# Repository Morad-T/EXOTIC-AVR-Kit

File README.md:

# AVR Kit

AVR Dev. Kit based on the ATmega32A

## Features

- Only 2 Layer PCB
- Can accomodate ZIF or normal 40-Pin sockets
- Over Current Protection
- CH340C USB to UART Interface
- Power Rail Selector
- Direct 10-Pin ISP Interface

## Yet To Be Done

- ICSP Header
- EMC Simulations

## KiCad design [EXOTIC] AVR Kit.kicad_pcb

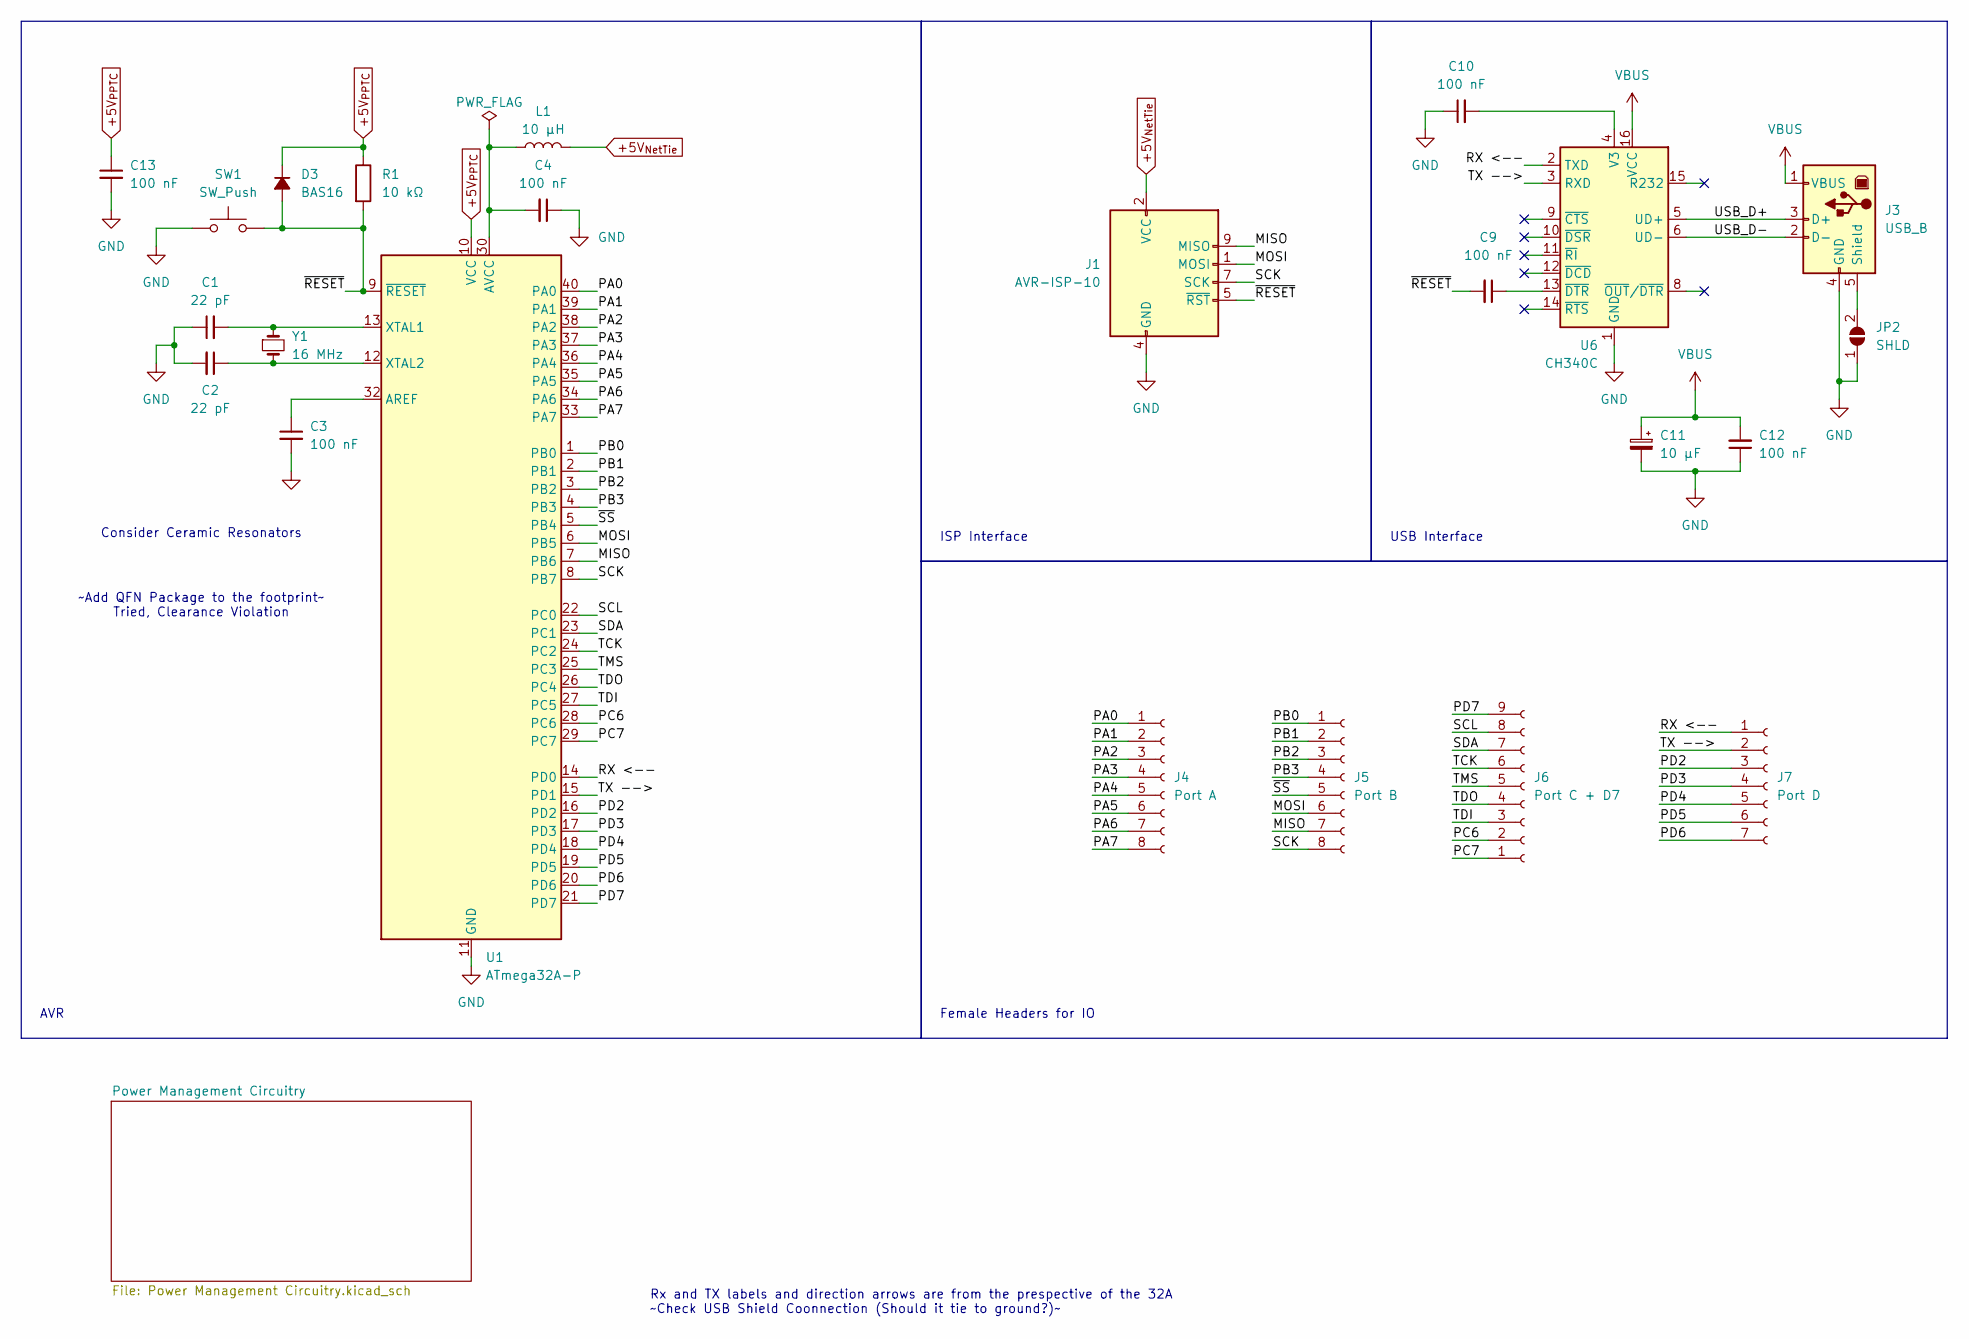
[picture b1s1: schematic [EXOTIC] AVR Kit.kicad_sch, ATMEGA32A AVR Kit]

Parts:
C1, C2: 22 pF; C_1206_3216Metric_Pad1.33x1.80mm_HandSolder
C3, C4, C9, C10, C12, C13: 100 nF; C_1206_3216Metric_Pad1.33x1.80mm_HandSolder
C11: 10 µF; C_1206_3216Metric_Pad1.33x1.80mm_HandSolder
D3: BAS16; SOT-23_Handsoldering
J1: AVR-ISP-10; IDC-Header_2x05_P2.54mm_Vertical
J3: USB_B; USB_B_Connector_Horizontal
J4: Port A; PinSocket_1x08_P2.54mm_Vertical
J5: Port B; PinSocket_1x08_P2.54mm_Vertical
J6: Port C + D7; PinSocket_1x09_P2.54mm_Vertical
J7: Port D; PinSocket_1x07_P2.54mm_Vertical
JP2: SHLD; SolderJumper-2_P1.3mm_Open_RoundedPad1.0x1.5mm
L1: 10 µH; L_1206_3216Metric_Pad1.22x1.90mm_HandSolder
R1: 10 kΩ; R_1206_3216Metric_Pad1.30x1.75mm_HandSolder
SW1: SW_Push; SW_PUSH_6mm_H4.3mm
U1: ATmega32A-P; ZIF_Socket_40_Circular_Pads
U6: CH340C; SOIC-16_3.9x9.9mm_P1.27mm
Y1: 16 MHz; Crystal_HC49-4H_Vertical_Centered

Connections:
+5V_{NetTie}: J1.2 (VCC), L1.1; also elsewhere on the board
+5V_{PPTC}: C13.1, D3.1 (K), R1.1, U1.10 (VCC); also elsewhere on the board
/MISO: J1.9 (MISO), J5.7, U1.7 (PB6)
/MOSI: J1.1 (MOSI), J5.6, U1.6 (PB5)
/PA0: J4.1, U1.40 (PA0)
/PA1: J4.2, U1.39 (PA1)
/PA2: J4.3, U1.38 (PA2)
/PA3: J4.4, U1.37 (PA3)
/PA4: J4.5, U1.36 (PA4)
/PA5: J4.6, U1.35 (PA5)
/PA6: J4.7, U1.34 (PA6)
/PA7: J4.8, U1.33 (PA7)
/PB0: J5.1, U1.1 (PB0)
/PB1: J5.2, U1.2 (PB1)
/PB2: J5.3, U1.3 (PB2)
/PB3: J5.4, U1.4 (PB3)
/PC6: J6.2, U1.28 (PC6)
/PC7: J6.1, U1.29 (PC7)
/PD2: J7.3, U1.16 (PD2)
/PD3: J7.4, U1.17 (PD3)
/PD4: J7.5, U1.18 (PD4)
/PD5: J7.6, U1.19 (PD5)
/PD6: J7.7, U1.20 (PD6)
/PD7: J6.9, U1.21 (PD7)
/RX <--: J7.1, U1.14 (PD0), U6.2 (TXD)
/SCK: J1.7 (SCK), J5.8, U1.8 (PB7)
/SCL: J6.8, U1.22 (PC0)
/SDA: J6.7, U1.23 (PC1)
/TCK: J6.6, U1.24 (PC2)
/TDI: J6.3, U1.27 (PC5)
/TDO: J6.4, U1.26 (PC4)
/TMS: J6.5, U1.25 (PC3)
/TX -->: J7.2, U1.15 (PD1), U6.3 (RXD)
/USB_D+: J3.3 (D+), U6.5 (UD+)
/USB_D-: J3.2 (D-), U6.6 (UD-)
/~RESET: C9.2, D3.2 (A), J1.5 (~RST), R1.2, SW1.1, U1.9 (~RESET)
/~SS: J5.5, U1.5 (PB4)
GND: C1.1, C2.2, C3.2, C4.1, C10.1, C11.2, C12.1, C13.2, J1.4 (GND), J1.6 (GND), J1.8 (GND), J1.10 (GND), J3.4 (GND), JP2.1 (A), SW1.2, U1.11 (GND), U1.31 (GND), U6.1 (GND); also elsewhere on the board
unnamed: J3.5 (Shield), JP2.2 (B)
unnamed: C3.1, U1.32 (AREF)
unnamed: C4.2, L1.2, U1.30 (AVCC)
unnamed: C1.2, U1.13 (XTAL1), Y1.1
unnamed: C2.1, U1.12 (XTAL2), Y1.2
unnamed: C10.2, U6.4 (V3)
unnamed: C9.1, U6.13 (~DTR)
VBUS: C11.1, C12.2, J3.1 (VBUS), U6.16 (VCC); also elsewhere on the board

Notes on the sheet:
Female Headers for IO
AVR
~Add QFN Package to the footprint~ Tried, Clearance Violation
ISP Interface
Consider Ceramic Resonators
Rx and TX labels and direction arrows are from the prespective of the 32A ~Check USB Shield Coonnection (Should it tie to ground?)~
USB Interface

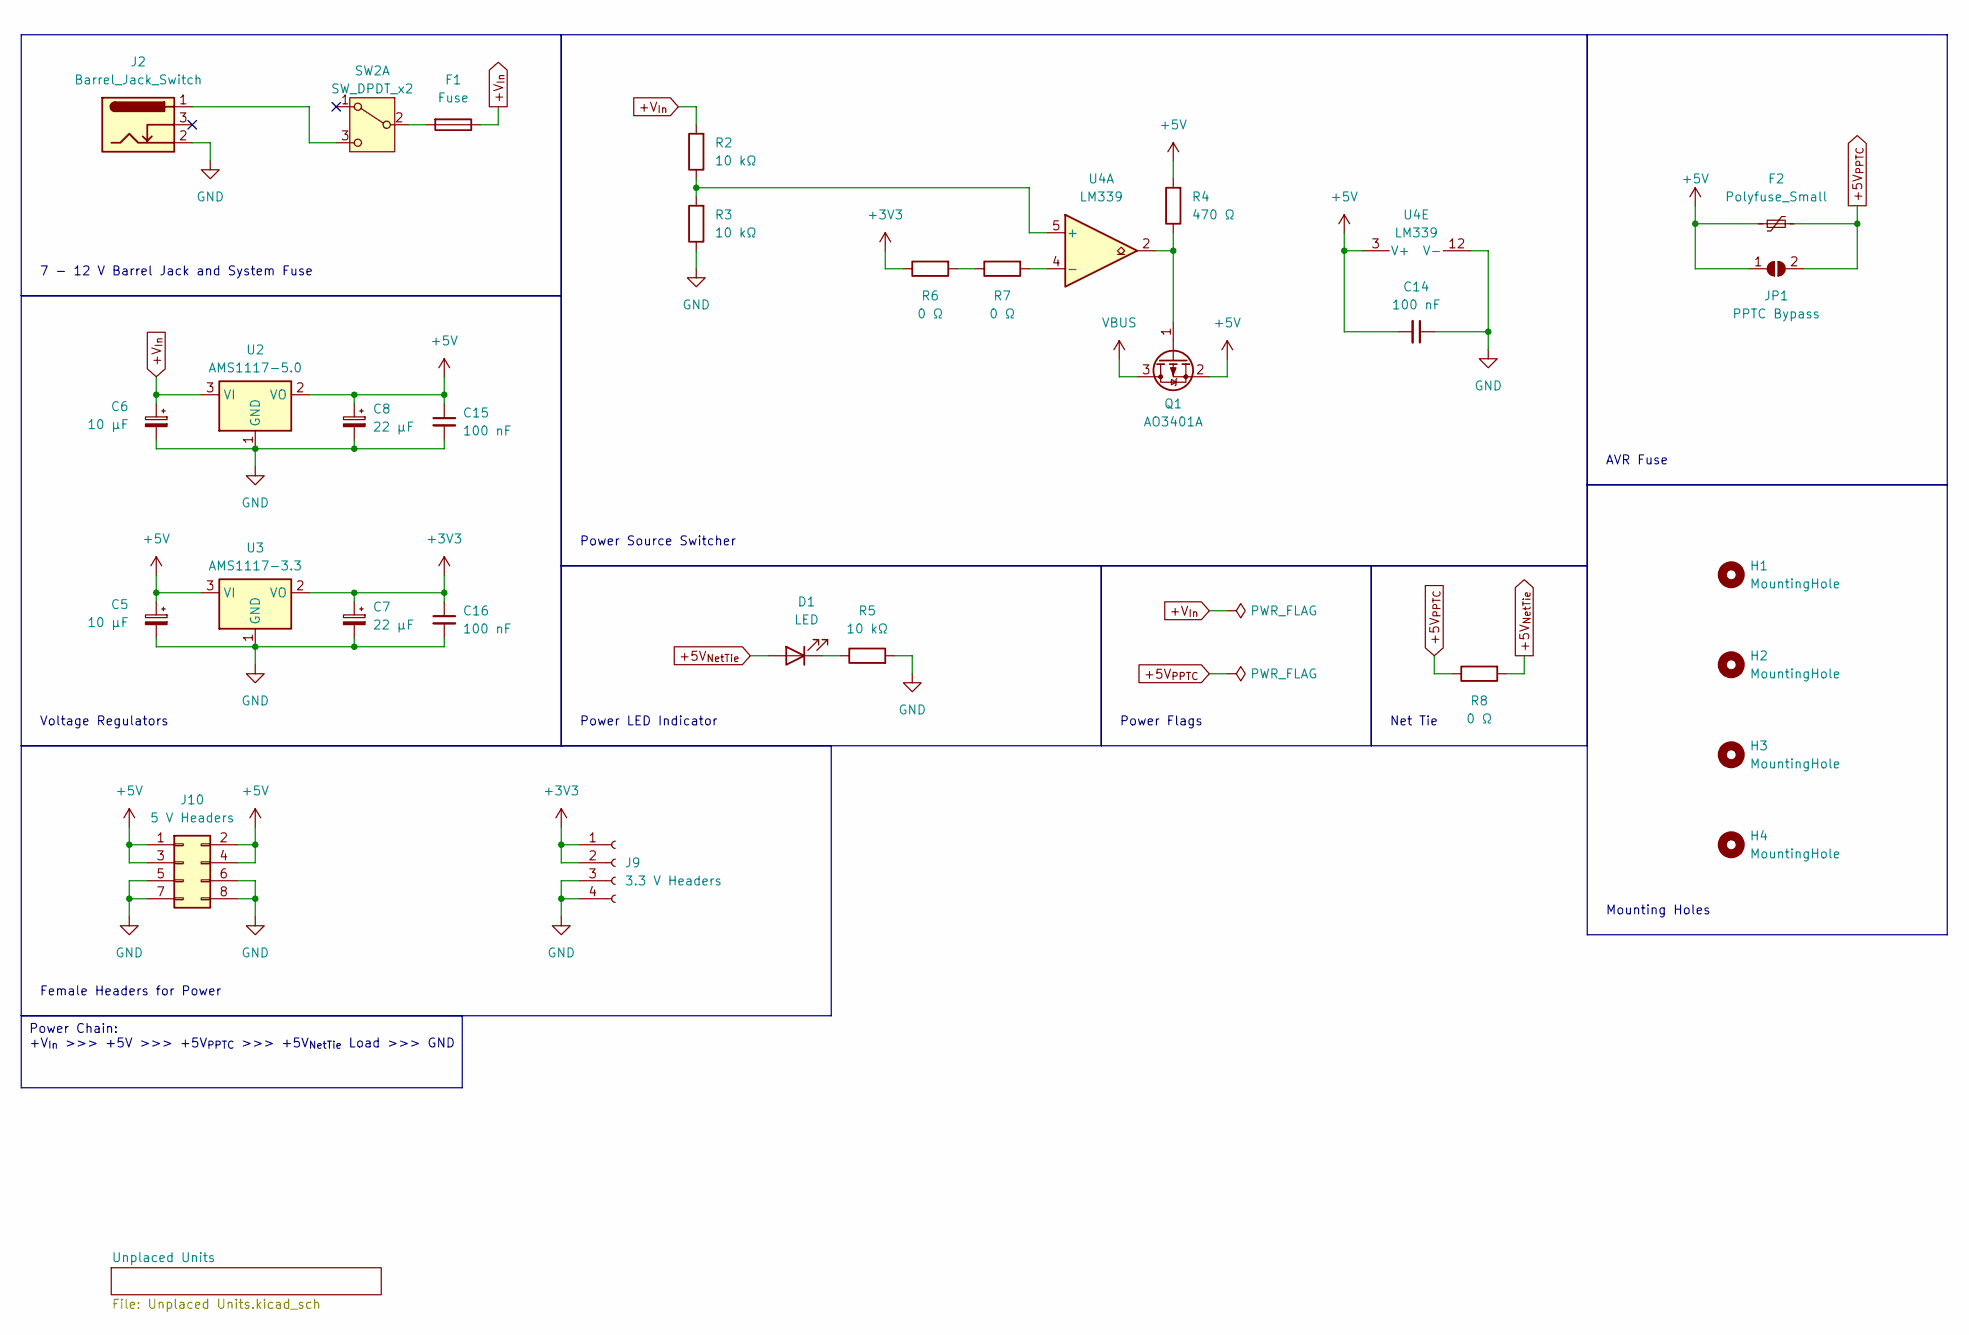
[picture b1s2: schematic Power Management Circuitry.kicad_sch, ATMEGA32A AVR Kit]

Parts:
C5, C6: 10 µF; C_1206_3216Metric_Pad1.33x1.80mm_HandSolder
C7, C8: 22 µF; C_1206_3216Metric_Pad1.33x1.80mm_HandSolder
C14, C15, C16: 100 nF; C_1206_3216Metric_Pad1.33x1.80mm_HandSolder
D1: LED; LED_1206_3216Metric_Pad1.42x1.75mm_HandSolder
F1: Fuse; Fuseholder_with_Cover_5x20mm_Horizontal
F2: Polyfuse_Small; Fuse_1206_3216Metric_Pad1.42x1.75mm_HandSolder
H1, H2, H3, H4: MountingHole; MountingHole_2.2mm_M2_Pad
J2: Barrel_Jack_Switch; BarrelJack_Horizontal
J9: 3.3 V Headers; PinSocket_1x04_P2.54mm_Vertical
J10: 5 V Headers; PinSocket_2x04_P2.54mm_Vertical
JP1: PPTC Bypass; SolderJumper-2_P1.3mm_Open_RoundedPad1.0x1.5mm
Q1: AO3401A; SOT-23_Handsoldering
R2, R3, R5: 10 kΩ; R_1206_3216Metric_Pad1.30x1.75mm_HandSolder
R4: 470 Ω; R_1206_3216Metric_Pad1.30x1.75mm_HandSolder
R6, R7, R8: 0 Ω; R_1206_3216Metric_Pad1.30x1.75mm_HandSolder
SW2: SW_DPDT_x2; SW_Push_DPDT_Toggle_7.0mm
U2: AMS1117-5.0; SOT-223-3_TabPin2
U3: AMS1117-3.3; SOT-223-3_TabPin2
U4: LM339; SOIC-14_3.9x8.7mm_P1.27mm

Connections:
+3V3: C7.1, C16.1, J9.1, J9.2, R6.1, U3.2 (VO)
+5V: C5.1, C8.1, C14.2, C15.1, F2.1, J10.1, J10.2, J10.3, J10.4, JP1.1 (A), Q1.2 (S), R4.2, U2.2 (VO), U3.3 (VI), U4.3 (V+)
+5V_{NetTie}: D1.2 (A), R8.2; also elsewhere on the board
+5V_{PPTC}: F2.2, JP1.2 (B), R8.1; also elsewhere on the board
+V_{In}: C6.1, F1.1, R2.2, U2.3 (VI)
GND: C5.2, C6.2, C7.2, C8.2, C14.1, C15.2, C16.2, J2.2, J9.3, J9.4, J10.5, J10.6, J10.7, J10.8, R3.1, R5.2, U2.1 (GND), U3.1 (GND), U4.12 (V-); also elsewhere on the board
unnamed: D1.1 (K), R5.1
unnamed: Q1.1 (G), R4.1, U4.2
unnamed: R6.2, R7.1
unnamed: F1.2, SW2.2 (B)
unnamed: J2.1, SW2.3 (C)
unnamed: R2.1, R3.2, U4.5 (+)
unnamed: R7.2, U4.4 (-)
VBUS: Q1.3 (D); also elsewhere on the board

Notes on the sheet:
Power Chain: +V_{In} >>> +5V >>> +5V_{PPTC} >>> +5V_{NetTie} Load >>> GND
Mounting Holes
Female Headers for Power
7 - 12 V Barrel Jack and System Fuse
AVR Fuse
Power LED Indicator
Power Source Switcher
Net Tie
Power Flags
Voltage Regulators

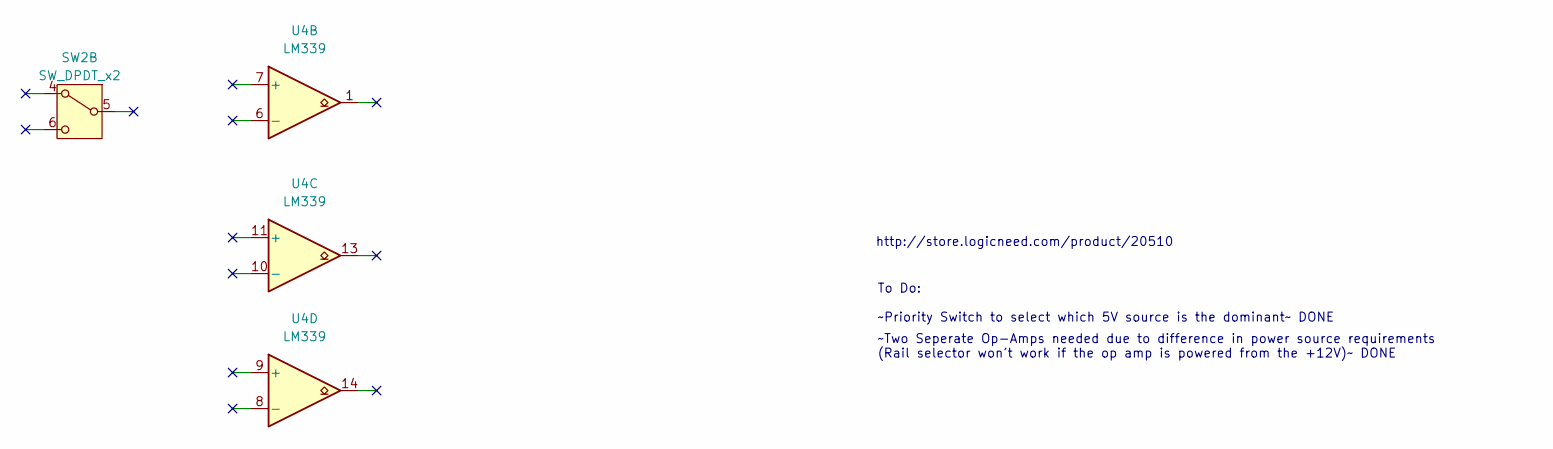
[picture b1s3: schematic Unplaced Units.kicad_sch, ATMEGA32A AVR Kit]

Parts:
SW2: SW_DPDT_x2; SW_Push_DPDT_Toggle_7.0mm
U4: LM339; SOIC-14_3.9x8.7mm_P1.27mm

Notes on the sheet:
http://store.logicneed.com/product/20510
~Two Seperate Op-Amps needed due to difference in power source requirements (Rail selector won't work if the op amp is powered from the +12V)~ DONE
To Do: ~Priority Switch to select which 5V source is the dominant~ DONE

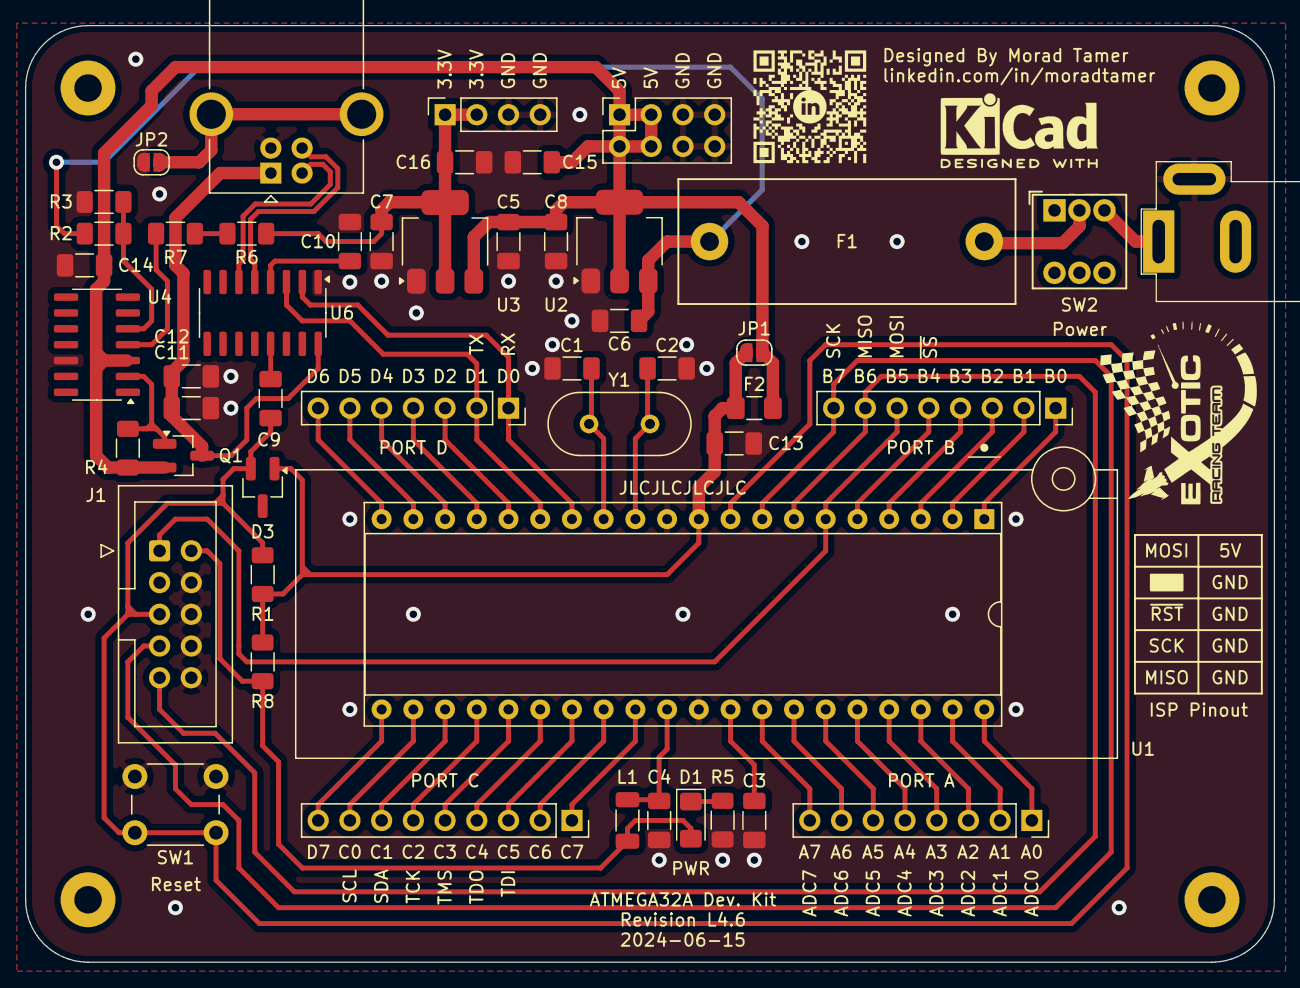
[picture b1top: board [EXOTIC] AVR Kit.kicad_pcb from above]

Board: 2 copper layers, 100.0 x 75.0 mm, 53 parts (0 on the bottom side), 56 nets.

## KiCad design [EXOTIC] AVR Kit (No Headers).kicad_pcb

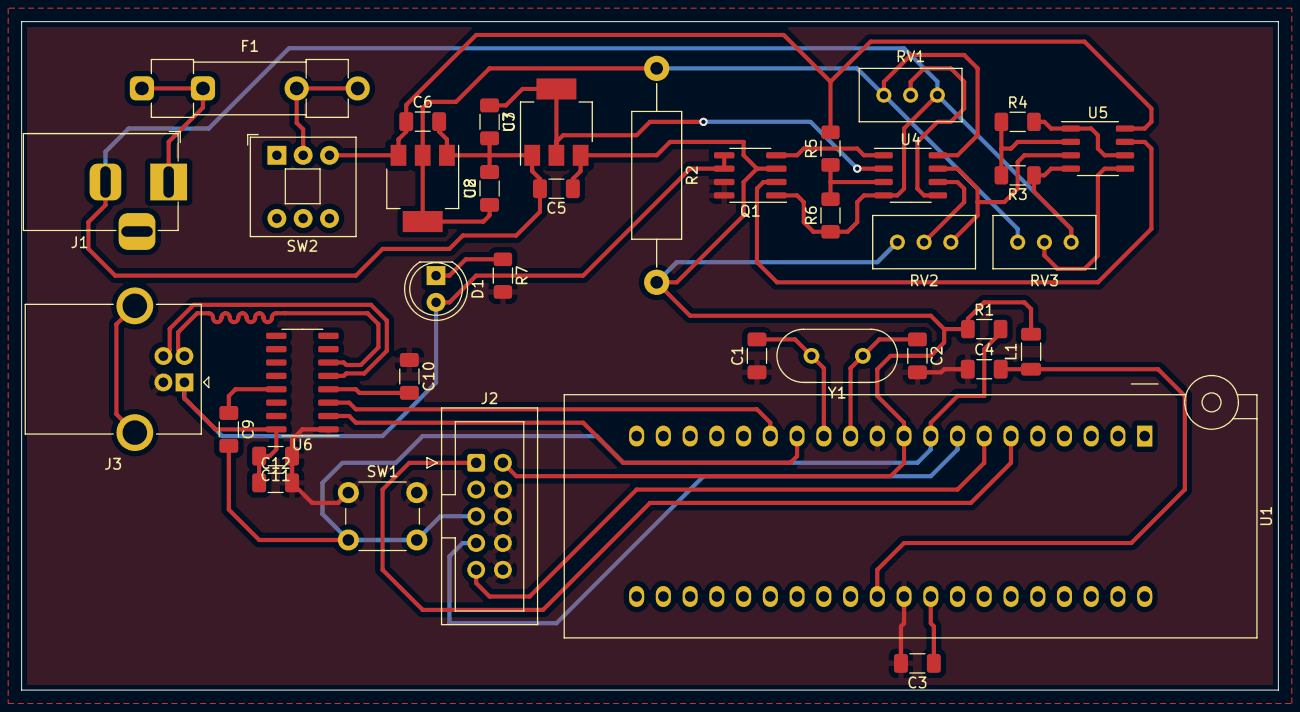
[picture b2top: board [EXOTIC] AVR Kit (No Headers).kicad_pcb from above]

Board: 2 copper layers, 119.4 x 63.5 mm, 38 parts (0 on the bottom side), 33 nets.

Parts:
C1, C2: 22 pF; C_1206_3216Metric_Pad1.33x1.80mm_HandSolder
C3, C4, C9, C10, C11: 100 nF; C_1206_3216Metric_Pad1.33x1.80mm_HandSolder
C5, C6, C12: 10 µF; C_1206_3216Metric_Pad1.33x1.80mm_HandSolder
C7, C8: 22 µF; C_1206_3216Metric_Pad1.33x1.80mm_HandSolder
D1: LED; LED_D5.0mm_Clear
F1: Fuse; Fuseholder_Clip-5x20mm_Littelfuse_520_Inline_P20.50x5.80mm_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
J1: Barrel_Jack_Switch; BarrelJack_Horizontal
J2: AVR-ISP-10; IDC-Header_2x05_P2.54mm_Vertical
J3: USB_B; USB_B_OST_USB-B1HSxx_Horizontal
L1: 10 µH; L_1206_3216Metric_Pad1.22x1.90mm_HandSolder
Q1: IRF7309IPBF; SOIC-8_3.9x4.9mm_P1.27mm
R1, R3, R6: 10 kΩ; R_1206_3216Metric_Pad1.30x1.75mm_HandSolder
R2: 100 mΩ; R_Axial_DIN0414_L11.9mm_D4.5mm_P20.32mm_Horizontal
R4: 330 kΩ; R_1206_3216Metric_Pad1.30x1.75mm_HandSolder
R5: 6k8 Ω; R_1206_3216Metric_Pad1.30x1.75mm_HandSolder
R7: 1 kΩ; R_1206_3216Metric_Pad1.30x1.75mm_HandSolder
RV1, RV2, RV3: 10 kΩ; Potentiometer_Bourns_3296W_Vertical
SW1: SW_Push; SW_PUSH_6mm_H4.3mm
SW2: SW_SPST; SW_Push_2P2T_Toggle_CK_PVA2xxH1xxxxxxV2
U1: ATmega32A-P; DIP_Socket-40_W11.9_W12.7_W15.24_W17.78_W18.5_3M_240-1280-0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
U2: AMS1117-5.0; SOT-223-3_TabPin2
U3: AMS1117-3.3; SOT-223-3_TabPin2
U4, U5: LM358; SO-8_3.9x4.9mm_P1.27mm
U6: CH340C; SOIC-16_3.9x9.9mm_P1.27mm
Y1: 16 MHz; Crystal_HC49-4H_Vertical

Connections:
+3V3: C7.1, U3.2 (VO), U4.2 (-)
+5V: C5.1, J2.2 (VCC), L1.2, Q1.3 (1), R1.1, R2.2, RV2.1, U1.10 (VCC), U3.3 (VI)
+5V_{OCP}: C8.1, R2.1, RV1.1, RV3.1, U2.2 (VO), U4.8 (V+)
+V_{In}: C6.1, R5.2, SW2.3 (C), U2.3 (VI), U5.8 (V+)
-V_{In}: C5.2, C6.2, C7.2, C8.2, J1.2, Q1.1 (S), R3.1, R6.1, RV1.3, RV3.3, U2.1 (GND), U3.1 (GND), U4.4 (V-), U5.4 (V-)
/MISO: J2.9 (MISO), U1.7 (PB6)
/MOSI: J2.1 (MOSI), U1.6 (PB5)
/RX <--: U1.14 (PD0), U6.2 (TXD)
/SCK: J2.7 (SCK), U1.8 (PB7)
/TX -->: U1.15 (PD1), U6.3 (RXD)
/USB_D+: J3.3 (D+), U6.5 (UD+)
/USB_D-: J3.2 (D-), U6.6 (UD-)
/~RESET: C9.2, J2.5 (~RST), R1.2, SW1.2, U1.9 (~RESET)
GND: C1.1, C2.2, C3.2, C4.1, C10.1, C11.1, C12.2, J2.4 (GND), J2.6 (GND), J2.8 (GND), J2.10 (GND), J3.4 (GND), Q1.7 (D), Q1.8 (D), R7.2, SW1.1, U1.11 (GND), U1.31 (GND), U6.1 (GND)
unnamed: D1.1 (K), R7.1
unnamed: F1.1, J1.1
unnamed: Q1.2 (G), U5.7
unnamed: Q1.4 (G), U4.1
unnamed: F1.2, SW2.2 (B)
unnamed: C3.1, U1.32 (AREF)
unnamed: C4.2, L1.1, U1.30 (AVCC)
unnamed: C1.2, U1.13 (XTAL1), Y1.2
unnamed: C2.1, U1.12 (XTAL2), Y1.1
unnamed: R5.1, R6.2, U4.3 (+)
unnamed: RV1.2, U4.5 (+)
unnamed: RV2.2, U4.6 (-)
unnamed: RV2.3, U4.7, U5.3 (+)
unnamed: R3.2, R4.1, U5.2 (-)
unnamed: RV3.2, U5.5 (+)
unnamed: R4.2, U5.1, U5.6 (-)
unnamed: C10.2, U6.4 (V3)
unnamed: C9.1, U6.13 (~DTR)
VBUS: C11.2, C12.1, D1.2 (A), J3.1 (VBUS), Q1.5 (D), Q1.6 (D), U6.16 (VCC)

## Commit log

2023-12-14 Images Exported From 3D View
2023-12-14 Finished recreating the schematic
    Created new footprints for DC Barrel Jack and Fuse Holder (3d models still require adjustment and finalize shunt resistance value and footprint)
2023-12-14 Schematic Revision C2
2023-12-14 Most work done
2023-12-14 WIP2
2023-12-14 Added The 3D Models
2023-12-14 done something
2023-12-14 Clean Up
2023-12-14 Schematic Touch Up
2023-12-14 PCB Touch Up
2023-12-14 Rev 2.1
2023-12-17 Update README.md
    Removed parenthesis to double check circuit operation
2023-12-20 Rev. 3
2023-12-20 Rev 3.1
2023-12-20 Some Tweaks
2023-12-20 Refresh
2023-12-22 Rev 3.2
    Cleaned Up Schematic
    Revised Layout
2023-12-22 Project File Update
2023-12-22 Added 5V and 3.3V O/P Pins
2023-12-22 Schematic Organization
2023-12-22 Updated Images
2023-12-22 Added My Initials
2024-01-05 Added I2C Labels
2024-01-05 Rounded Corners
2024-01-05 Some Touch Ups
2024-01-05 Improved Schematics' Readability
2024-01-06 More Touch Ups
    Tidied the schematic
    Added Dimensions of the PCB on User.Drawings Layer
2024-01-14 New Subrevision
2024-01-14 Minor Tweak
2024-01-24 More Tweaks
2024-02-04 Pre Rev. 4
2024-02-26 Create LICENSE
2024-03-07 Rev 3.99
2024-03-07 Images Updates
2024-03-07 Rev. L4.2
2024-03-26 Auto-Reset Circuit Simulation
2024-05-13 Migrated from KiCAD 7.0 to 8.0
2024-06-15 Removed the two LED indicators
    Removed the two LED indicators for each power source and replaced them with a single LED for the final 5V rail
2024-08-24 Actually I don't remember
